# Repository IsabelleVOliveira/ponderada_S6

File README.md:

# Atividade Ponderada - Placa de circuito impresso com Raspberry Pi Pico

Atividade realizada por Isabelle Beatriz Vasquez Oliveira

Para a entrega dessa atividade, foi desenvolvido uma placa de circuito impresso contendo: 

- 1 Raspberry pi pico;
- 1 Transistor;
- 1 LED;
- 1 pino de saída.

Nesse repositório, foi entregue o arquivo da PCB Esquemático e o arquivo GBR para impressão da placa.

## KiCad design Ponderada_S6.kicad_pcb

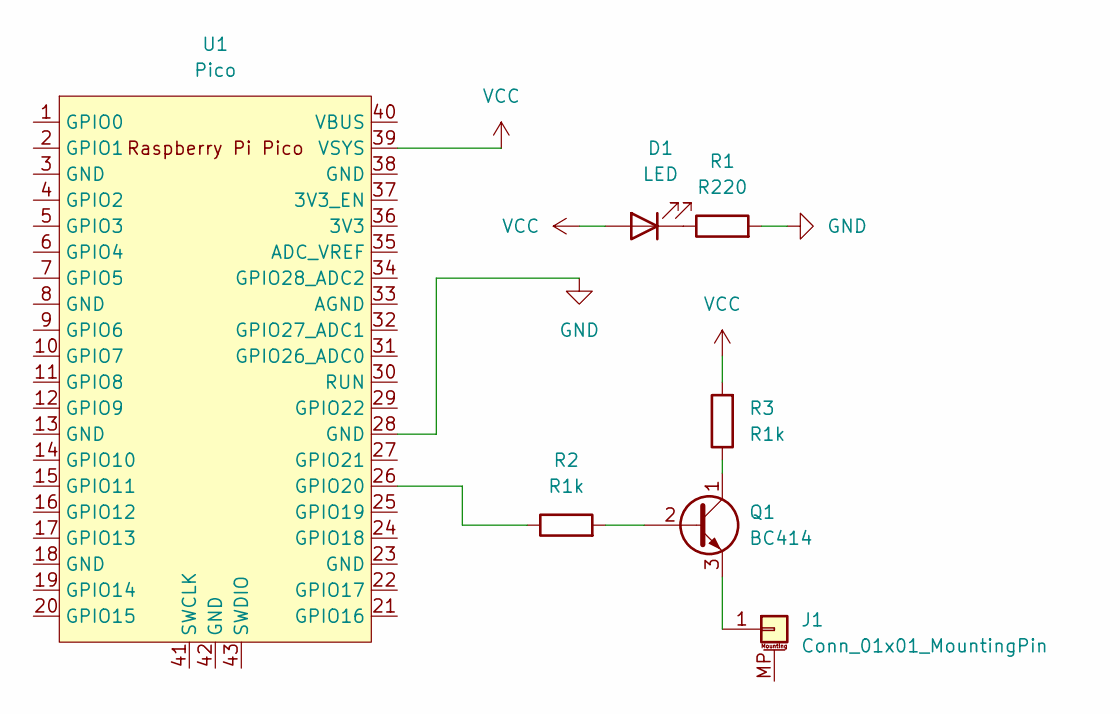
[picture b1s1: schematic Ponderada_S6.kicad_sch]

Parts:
D1: LED; LED_Rectangular_W5.0mm_H2.0mm
J1: Conn_01x01_MountingPin; JST_ACH_BM01B-ACHSS-A-GAN-ETF_1x01-1MP_P1.20mm_Vertical
Q1: BC414; TO-92_Inline
R1: R220; R_Axial_DIN0204_L3.6mm_D1.6mm_P2.54mm_Vertical
R2, R3: R1k; R_Axial_DIN0204_L3.6mm_D1.6mm_P2.54mm_Vertical
U1: Pico; RPi_Pico_SMD_TH

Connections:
GND: R1.2, U1.28 (GND)
unnamed: D1.1 (K), R1.1
unnamed: J1.1, Q1.3 (E)
unnamed: Q1.2 (B), R2.2
unnamed: Q1.1 (C), R3.1
unnamed: R2.1, U1.26 (GPIO20)
VCC: D1.2 (A), R3.2, U1.39 (VSYS)

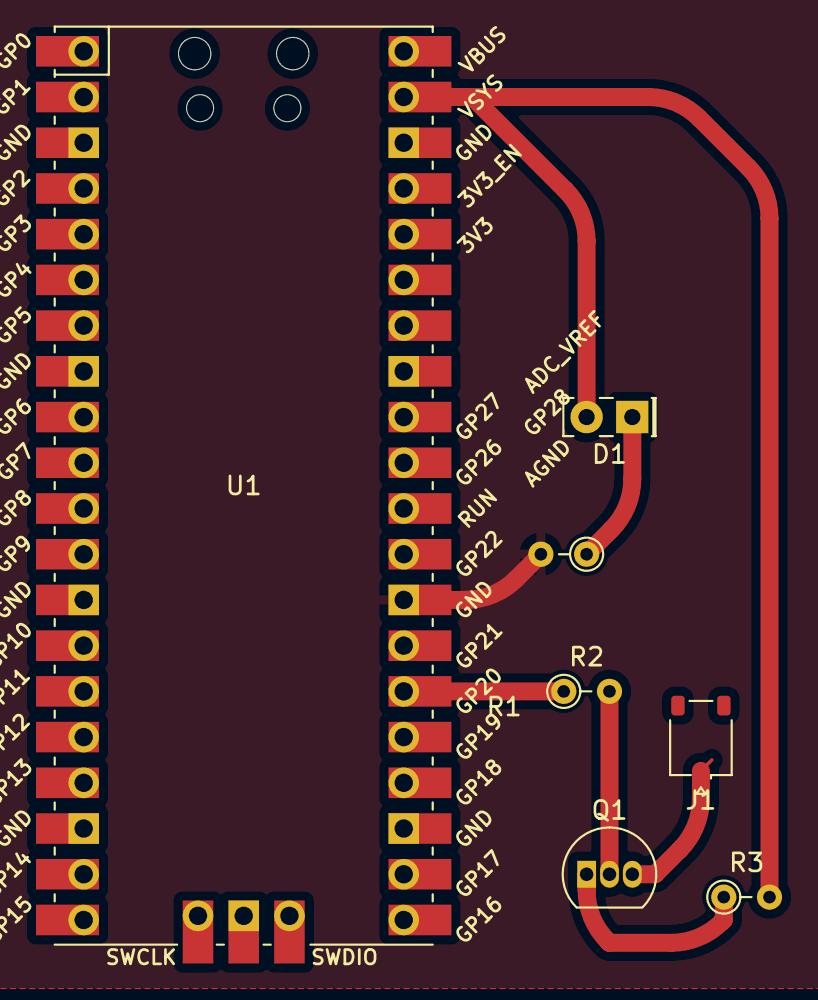
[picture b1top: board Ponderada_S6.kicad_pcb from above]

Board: 2 copper layers, 7 parts (0 on the bottom side), 7 nets.

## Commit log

2024-03-27 ponderada no kicad
